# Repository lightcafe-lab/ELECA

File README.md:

# ELECA
ELECA（エレカ）は**CC BY-SA4.0ライセンス**で**名刺デザイン**の**Arduino互換機**です<br>
LIGHTCAFE LAB ELECA 作品ページはこちら<br>
https://lab.lightcafe.co.jp/work/eleca<br>

## firmware
ELECAに書き込むArduinoのサンプルスケッチです<br>
給電すると動作がはじまります<br>

*eleca-ble-write*<br>
Bluetoothの子機（peripheral）になります<br>

*eleca-hand-pov*<br>
ハンディのバーサライタになります<br>

*eleca-stand*<br>
レインボーが流れていきます<br>

## hardware
ELECA付属のハードウェアです<br>

*3d-print-options*<br>
3DプリントできるELECA専用スタンドです<br>

*acryl-cover*<br>
ELECAの専用アクリルカバーです<br>

## pcb
KiCad (v8.0.3)を使用した回路図と基板図です<br>

*pcb-eleca*<br>
ELECAのメイン基板<br>

*pcb-eleca-extend*<br>
ELECAの拡張スロット用基板<br>
・拡張基板1（加速度センサ）<br>
・拡張基板2（フルカラーLED＋スイッチ）<br>

# ライセンスについて
この 作品 は <a rel="license" href="https://creativecommons.org/licenses/by-sa/4.0/deed.ja">クリエイティブ・コモンズ 表示 - 継承 4.0 国際 ライセンス</a>の下に提供されています<br>
<br />

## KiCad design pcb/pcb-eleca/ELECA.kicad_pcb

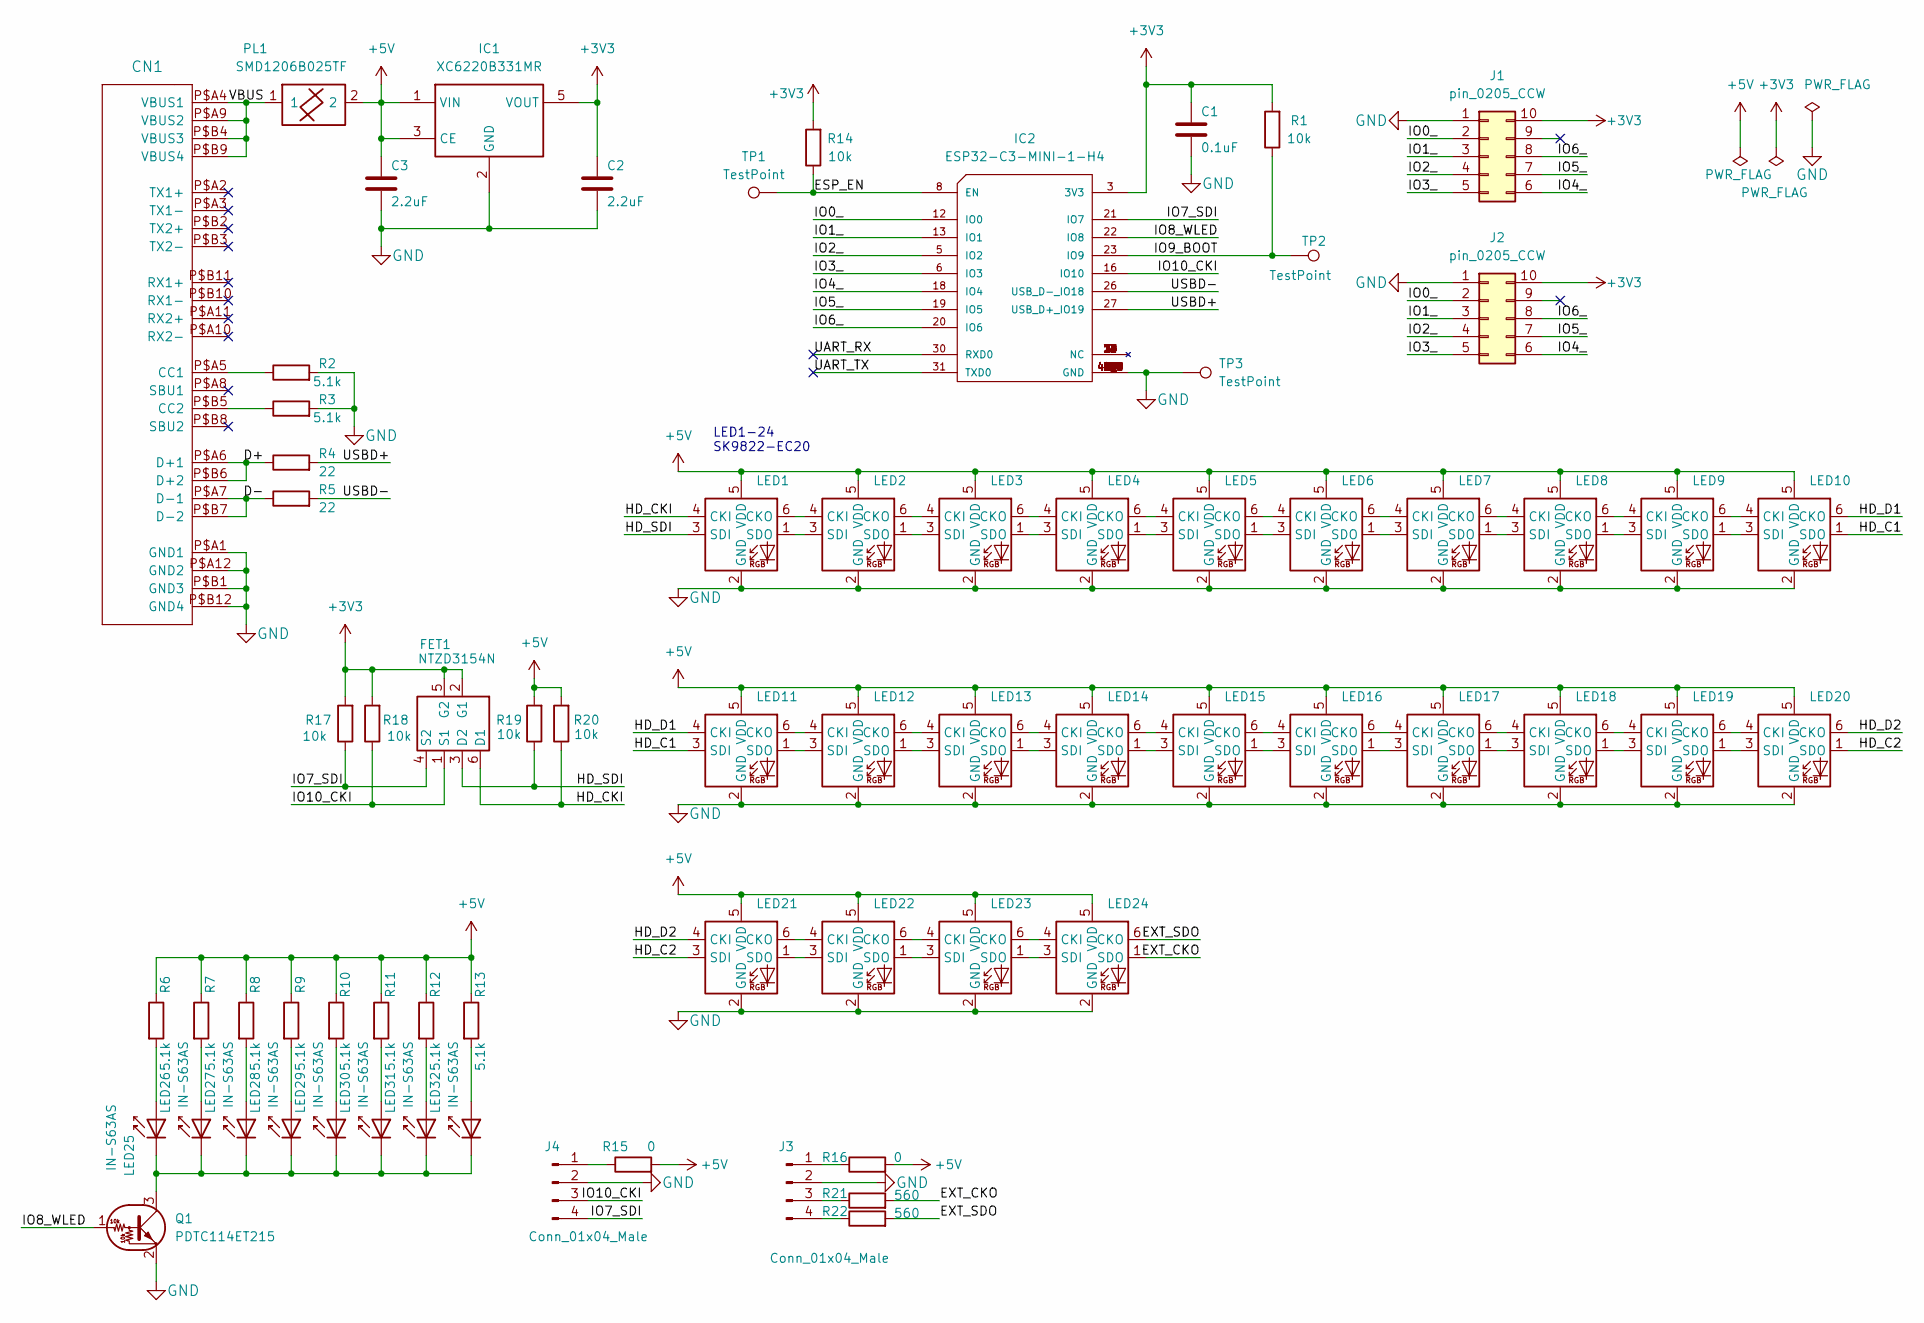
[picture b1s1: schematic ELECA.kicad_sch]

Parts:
C1: 0.1uF; C_0603_1608Metric
C2, C3: 2.2uF; C_0603_1608Metric
CN1: CON_USB-CPCBPLUG; USB-C_PCBPLUG
FET1: NTZD3154N; NTZD3154NT1G
IC1: XC6220B331MR; SOT-23-5
IC2: ESP32-C3-MINI-1-H4; XCVR_ESP32-C3-MINI-1-N4
J1, J2: pin_0205_CCW; if-8080-10pin-mount-HAT
J3, J4: Conn_01x04_Male; 1×04_pinhead_smd
LED1, LED2, LED3, LED4, LED5, LED6, LED7, LED8, LED9, LED10, LED11, LED12, LED13, LED14, LED15, LED16, LED17, LED18, LED19, LED20, LED21, LED22, LED23, LED24: SK9822-EC20
LED25, LED26, LED27, LED28, LED29, LED30, LED31, LED32: IN-S63AS; IN-S63AS5UW
PL1: SMD1206B025TF; R_1206_3216Metric
Q1: PDTC114ET215; SOT-23-3
R1, R14, R17, R18, R19, R20: 10k; R_0603_1608Metric
R2, R3, R6, R7, R8, R9, R10, R11, R12, R13: 5.1k; R_0603_1608Metric
R4, R5: 22; R_0603_1608Metric
R15, R16: 0; R_0603_1608Metric
R21, R22: 560; R_0603_1608Metric
TP1, TP2, TP3: TestPoint; TestPoint_Pad_D1.5mm

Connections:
+3V3: C1.1, C2.1, FET1.2 (G1), FET1.5 (G2), IC1.5 (VOUT), IC2.3 (3V3), J1.10, J2.10, R1.2, R14.2, R17.2, R18.2
+5V: C3.1, IC1.1 (VIN), IC1.3 (CE), LED1.5 (VDD), LED2.5 (VDD), LED3.5 (VDD), LED4.5 (VDD), LED5.5 (VDD), LED6.5 (VDD), LED7.5 (VDD), LED8.5 (VDD), LED9.5 (VDD), LED10.5 (VDD), LED11.5 (VDD), LED12.5 (VDD), LED13.5 (VDD), LED14.5 (VDD), LED15.5 (VDD), LED16.5 (VDD), LED17.5 (VDD), LED18.5 (VDD), LED19.5 (VDD), LED20.5 (VDD), LED21.5 (VDD), LED22.5 (VDD), LED23.5 (VDD), LED24.5 (VDD), PL1.2, R6.1, R7.1, R8.1, R9.1, R10.1, R11.1, R12.1, R13.1, R15.2, R16.2, R19.2, R20.2
/D+: CN1.P$A6 (D+1), CN1.P$B6 (D+2), R4.1
/D-: CN1.P$A7 (D-1), CN1.P$B7 (D-2), R5.1
/ESP_EN: IC2.8 (EN), R14.1, TP1.1
/EXT_CKO: LED24.1 (SDO), R21.2
/EXT_SDO: LED24.6 (CKO), R22.2
/HD_C1: LED10.1 (SDO), LED11.3 (SDI)
/HD_C2: LED20.1 (SDO), LED21.3 (SDI)
/HD_CKI: FET1.6 (D1), LED1.4 (CKI), R20.1
/HD_D1: LED10.6 (CKO), LED11.4 (CKI)
/HD_D2: LED20.6 (CKO), LED21.4 (CKI)
/HD_SDI: FET1.3 (D2), LED1.3 (SDI), R19.1
/IO0_: IC2.12 (IO0), J1.2, J2.2
/IO1_: IC2.13 (IO1), J1.3, J2.3
/IO2_: IC2.5 (IO2), J1.4, J2.4
/IO3_: IC2.6 (IO3), J1.5, J2.5
/IO4_: IC2.18 (IO4), J1.6, J2.6
/IO5_: IC2.19 (IO5), J1.7, J2.7
/IO6_: IC2.20 (IO6), J1.8, J2.8
/IO7_SDI: FET1.4 (S2), IC2.21 (IO7), J4.4, R17.1
/IO8_WLED: IC2.22 (IO8), Q1.1 (B)
/IO9_BOOT: IC2.23 (IO9), R1.1, TP2.1
/IO10_CKI: FET1.1 (S1), IC2.16 (IO10), J4.3, R18.1
/UART_RX: IC2.30 (RXD0)
/UART_TX: IC2.31 (TXD0)
/USBD+: IC2.27 (USB_D+_IO19), R4.2
/USBD-: IC2.26 (USB_D-_IO18), R5.2
/VBUS: CN1.P$A4 (VBUS1), CN1.P$A9 (VBUS2), CN1.P$B4 (VBUS3), CN1.P$B9 (VBUS4), PL1.1
GND: C1.2, C2.2, C3.2, CN1.P$A1 (GND1), CN1.P$A12 (GND2), CN1.P$B1 (GND3), CN1.P$B12 (GND4), IC1.2 (GND), IC2.1 (GND), IC2.2 (GND), IC2.11 (GND), IC2.14 (GND), IC2.36 (GND), IC2.37 (GND), IC2.38 (GND), IC2.39 (GND), IC2.40 (GND), IC2.41 (GND), IC2.42 (GND), IC2.43 (GND), IC2.44 (GND), IC2.45 (GND), IC2.46 (GND), IC2.47 (GND), IC2.48 (GND), IC2.49_1 (GND), IC2.49_2 (GND), IC2.49_3 (GND), IC2.49_4 (GND), IC2.49_5 (GND), IC2.49_6 (GND), IC2.49_7 (GND), IC2.49_8 (GND), IC2.49_9 (GND), IC2.50 (GND), IC2.51 (GND), IC2.52 (GND), IC2.53 (GND), J1.1, J2.1, J3.2, J4.2, LED1.2 (GND), LED2.2 (GND), LED3.2 (GND), LED4.2 (GND), LED5.2 (GND), LED6.2 (GND), LED7.2 (GND), LED8.2 (GND), LED9.2 (GND), LED10.2 (GND), LED11.2 (GND), LED12.2 (GND), LED13.2 (GND), LED14.2 (GND), LED15.2 (GND), LED16.2 (GND), LED17.2 (GND), LED18.2 (GND), LED19.2 (GND), LED20.2 (GND), LED21.2 (GND), LED22.2 (GND), LED23.2 (GND), LED24.2 (GND), Q1.2 (E), R2.2, R3.2, TP3.1
unnamed: CN1.P$A5 (CC1), R2.1
unnamed: CN1.P$B5 (CC2), R3.1
unnamed: J3.1, R16.1
unnamed: J3.3, R21.1
unnamed: J3.4, R22.1
unnamed: J4.1, R15.1
unnamed: LED1.6 (CKO), LED2.4 (CKI)
unnamed: LED1.1 (SDO), LED2.3 (SDI)
unnamed: LED2.6 (CKO), LED3.4 (CKI)
unnamed: LED2.1 (SDO), LED3.3 (SDI)
unnamed: LED3.6 (CKO), LED4.4 (CKI)
unnamed: LED3.1 (SDO), LED4.3 (SDI)
unnamed: LED4.6 (CKO), LED5.4 (CKI)
unnamed: LED4.1 (SDO), LED5.3 (SDI)
unnamed: LED5.6 (CKO), LED6.4 (CKI)
unnamed: LED5.1 (SDO), LED6.3 (SDI)
unnamed: LED6.6 (CKO), LED7.4 (CKI)
unnamed: LED6.1 (SDO), LED7.3 (SDI)
unnamed: LED7.6 (CKO), LED8.4 (CKI)
unnamed: LED7.1 (SDO), LED8.3 (SDI)
unnamed: LED8.6 (CKO), LED9.4 (CKI)
unnamed: LED8.1 (SDO), LED9.3 (SDI)
unnamed: LED9.6 (CKO), LED10.4 (CKI)
unnamed: LED9.1 (SDO), LED10.3 (SDI)
unnamed: LED11.6 (CKO), LED12.4 (CKI)
unnamed: LED11.1 (SDO), LED12.3 (SDI)
unnamed: LED12.6 (CKO), LED13.4 (CKI)
unnamed: LED12.1 (SDO), LED13.3 (SDI)
unnamed: LED13.6 (CKO), LED14.4 (CKI)
unnamed: LED13.1 (SDO), LED14.3 (SDI)
unnamed: LED14.6 (CKO), LED15.4 (CKI)
unnamed: LED14.1 (SDO), LED15.3 (SDI)
unnamed: LED15.6 (CKO), LED16.4 (CKI)
unnamed: LED15.1 (SDO), LED16.3 (SDI)
unnamed: LED16.6 (CKO), LED17.4 (CKI)
unnamed: LED16.1 (SDO), LED17.3 (SDI)
unnamed: LED17.6 (CKO), LED18.4 (CKI)
unnamed: LED17.1 (SDO), LED18.3 (SDI)
unnamed: LED18.6 (CKO), LED19.4 (CKI)
unnamed: LED18.1 (SDO), LED19.3 (SDI)
unnamed: LED19.6 (CKO), LED20.4 (CKI)
unnamed: LED19.1 (SDO), LED20.3 (SDI)
unnamed: LED21.6 (CKO), LED22.4 (CKI)
unnamed: LED21.1 (SDO), LED22.3 (SDI)
unnamed: LED22.6 (CKO), LED23.4 (CKI)
unnamed: LED22.1 (SDO), LED23.3 (SDI)
unnamed: LED23.6 (CKO), LED24.4 (CKI)
unnamed: LED23.1 (SDO), LED24.3 (SDI)
unnamed: LED25.2 (A), R6.2
unnamed: LED25.1 (K), LED26.1 (K), LED27.1 (K), LED28.1 (K), LED29.1 (K), LED30.1 (K), LED31.1 (K), LED32.1 (K), Q1.3 (C)
unnamed: LED26.2 (A), R7.2
unnamed: LED27.2 (A), R8.2
unnamed: LED28.2 (A), R9.2
unnamed: LED29.2 (A), R10.2
unnamed: LED30.2 (A), R11.2
unnamed: LED31.2 (A), R12.2
unnamed: LED32.2 (A), R13.2

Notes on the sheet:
LED1-24 SK9822-EC20

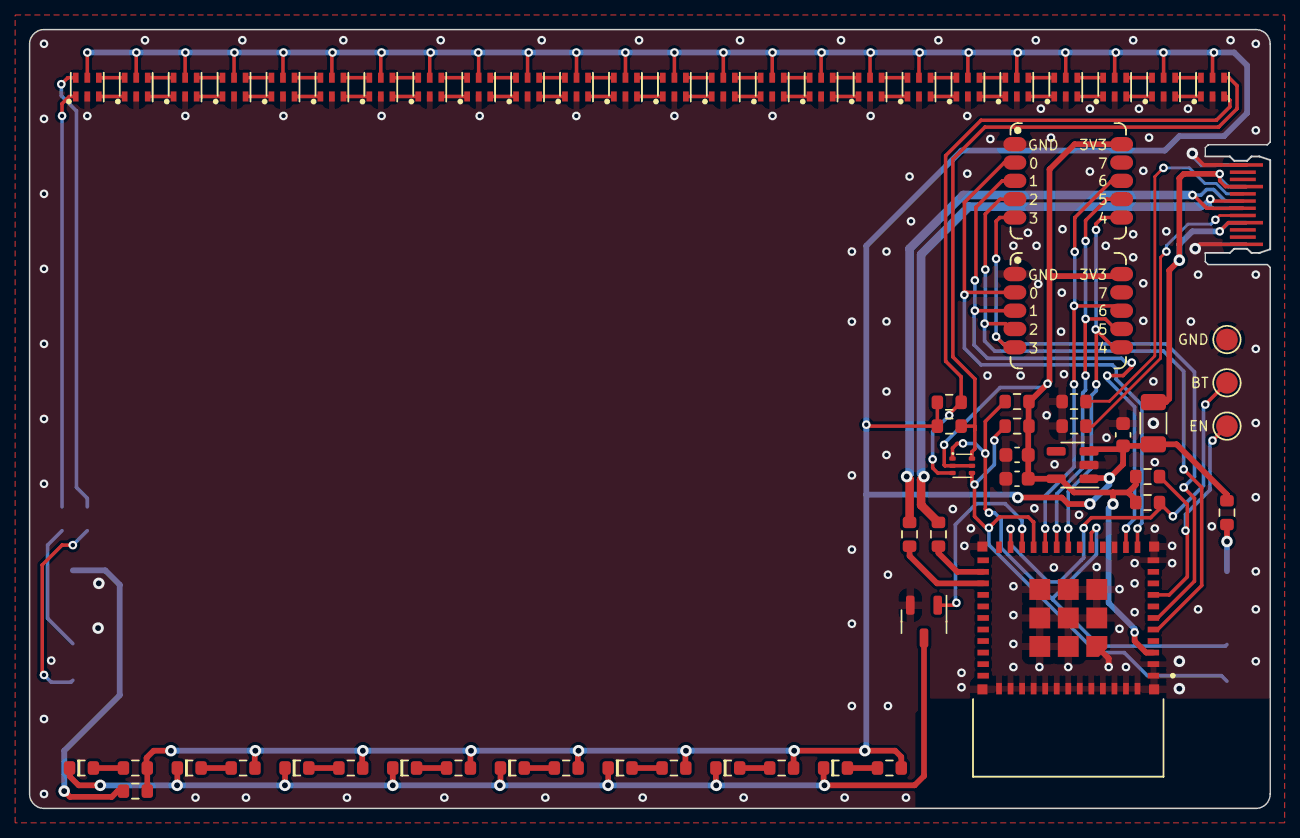
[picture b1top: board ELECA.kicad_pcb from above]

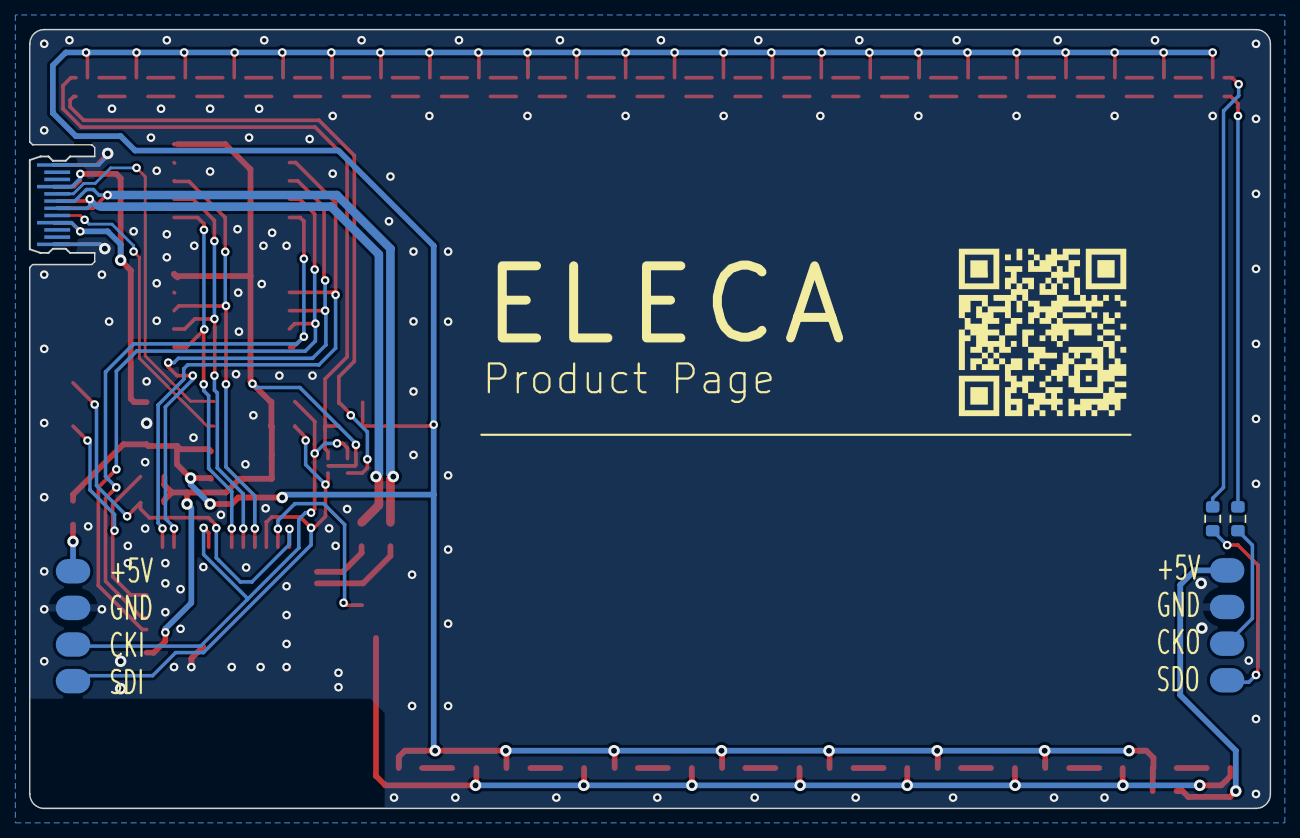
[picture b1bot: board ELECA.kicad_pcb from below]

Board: 2 copper layers, 86.0 x 54.0 mm, 70 parts (4 on the bottom side), 85 nets.

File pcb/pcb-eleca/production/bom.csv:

Designator,Footprint,Quantity,Value,LCSC Part #
C1,0603,1,0.1uF,
"C2, C3",0603,2,2.2uF,
CN1,USB-C_PCBPLUG,1,CON_USB-CPCBPLUG,
IC1,SOT-23-5,1,XC6220B331MR,
IC2,XCVR_ESP32-C3-MINI-1-N4,1,ESP32-C3-MINI-1-H4,
"J1, J2",if-8080-10pin-mount-HAT,2,pin_0205_CCW,
"J3, J4",1×04_pinhead_smd,2,Conn_01x04_Male,
"LED1, LED10, LED11, LED12, LED13, LED14, LED15, LED16, LED17, LED18, LED19, LED2, LED20, LED21, LED22, LED23, LED24, LED3, LED4, LED5, LED6, LED7, LED8, LED9",HD107S-2020,24,HD107S-2020,
"LED25, LED26, LED27, LED28, LED29, LED30, LED31, LED32",IN-S63AS5UW,8,IN-S63AS,
PL1,1206,1,SMD1206B025TF,
Q1,SOT-23-3,1,PDTC114ET215,
"R1, R14",0603,2,10k,
"R10, R11, R12, R13, R2, R3, R6, R7, R8, R9",0603,10,5.1k,
"R15, R16",0603,2,0,
"R4, R5",0603,2,22,
"TP1, TP2, TP3",TestPoint_Pad_D1.5mm,3,TestPoint,

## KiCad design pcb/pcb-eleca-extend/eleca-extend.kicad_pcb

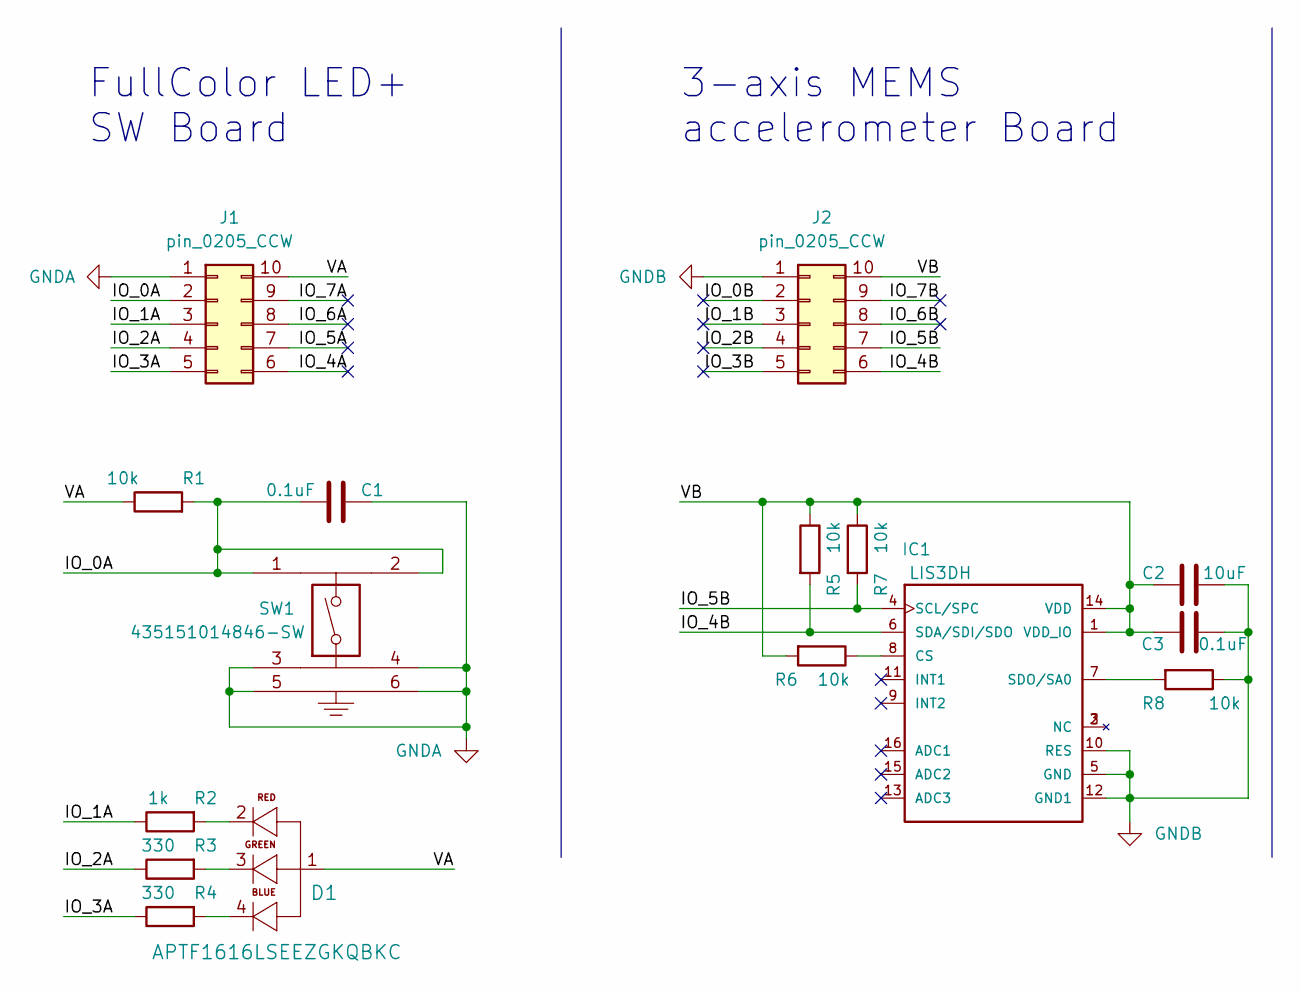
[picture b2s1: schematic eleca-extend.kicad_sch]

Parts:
C1, C3: 0.1uF; C_0402_1005Metric
C2: 10uF; C_0603_1608Metric
D1: APTF1616LSEEZGKQBKC; LED_APTF1616LSEEZGKQBKC
IC1: LIS3DH
J1, J2: pin_0205_CCW; hachi-8080-10pin-castle
R1, R5, R6, R7, R8: 10k; R_0402_1005Metric
R2: 1k; R_0402_1005Metric
R3, R4: 330; R_0402_1005Metric
SW1: 435151014846-SW; 435151014846

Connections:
/IO_0A: C1.2, J1.2, R1.2, SW1.1, SW1.2
/IO_0B: J2.2
/IO_1A: J1.3, R2.1
/IO_1B: J2.3
/IO_2A: J1.4, R3.1
/IO_2B: J2.4
/IO_3A: J1.5, R4.1
/IO_3B: J2.5
/IO_4A: J1.6
/IO_4B: IC1.6 (SDA/SDI/SDO), J2.6, R5.2
/IO_5A: J1.7
/IO_5B: IC1.4 (SCL/SPC), J2.7, R7.2
/IO_6A: J1.8
/IO_6B: J2.8
/IO_7A: J1.9
/IO_7B: J2.9
/VA: D1.1, J1.10, R1.1
/VB: C2.1, C3.1, IC1.1 (VDD_IO), IC1.14 (VDD), J2.10, R5.1, R6.2, R7.1
GNDA: C1.1, J1.1, SW1.3, SW1.4, SW1.5, SW1.6
GNDB: C2.2, C3.2, IC1.5 (GND), IC1.10 (RES), IC1.12 (GND1), J2.1, R8.1
unnamed: D1.2, R2.2
unnamed: D1.3, R3.2
unnamed: D1.4, R4.2
unnamed: IC1.7 (SDO/SA0), R8.2
unnamed: IC1.8 (CS), R6.1

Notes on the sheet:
3-axis MEMS accelerometer Board
FullColor LED+ SW Board

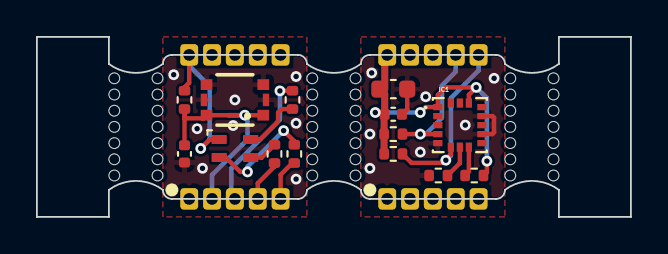
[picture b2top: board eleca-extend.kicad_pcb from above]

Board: 2 copper layers, 33.0 x 10.0 mm, 16 parts (0 on the bottom side), 15 nets.

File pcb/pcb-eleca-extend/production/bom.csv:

Designator,Footprint,Quantity,Value,LCSC Part #
"C1, C3",0402,2,0.1uF,
C2,0603,1,10uF,
D1,LED_APTF1616LSEEZGKQBKC,1,APTF1616LSEEZGKQBKC,
IC1,LIS3DH,1,LIS3DH,
"J1, J2",hachi-8080-10pin-castle,2,pin_0205_CCW,
"R1, R5, R6, R7, R8",0402,5,10k,
R2,0402,1,1k,
"R3, R4",0402,2,330,
SW1,435151014846,1,435151014846-SW,

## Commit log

2023-10-17 Update README.md
    add thumbnail
2023-10-19 add thumbnail
2024-09-24 update-v0.1.0
2024-09-25 fix-README
2024-09-25 fix-acryl-cover
2024-09-25 fix-arduino-sketch
2024-09-25 fix-eleca-pcb
